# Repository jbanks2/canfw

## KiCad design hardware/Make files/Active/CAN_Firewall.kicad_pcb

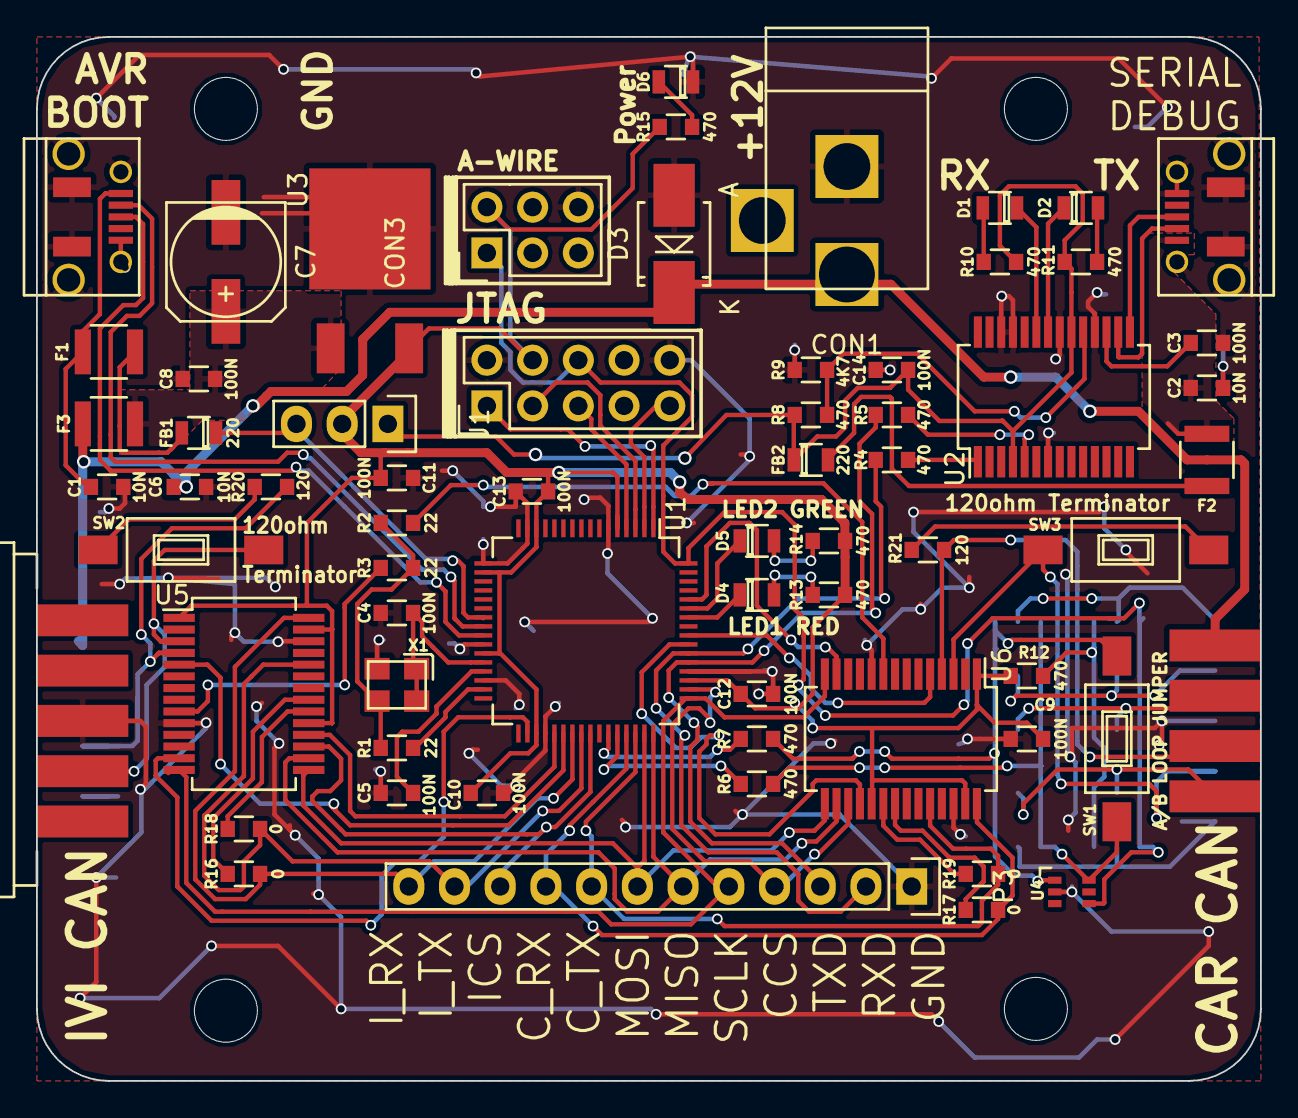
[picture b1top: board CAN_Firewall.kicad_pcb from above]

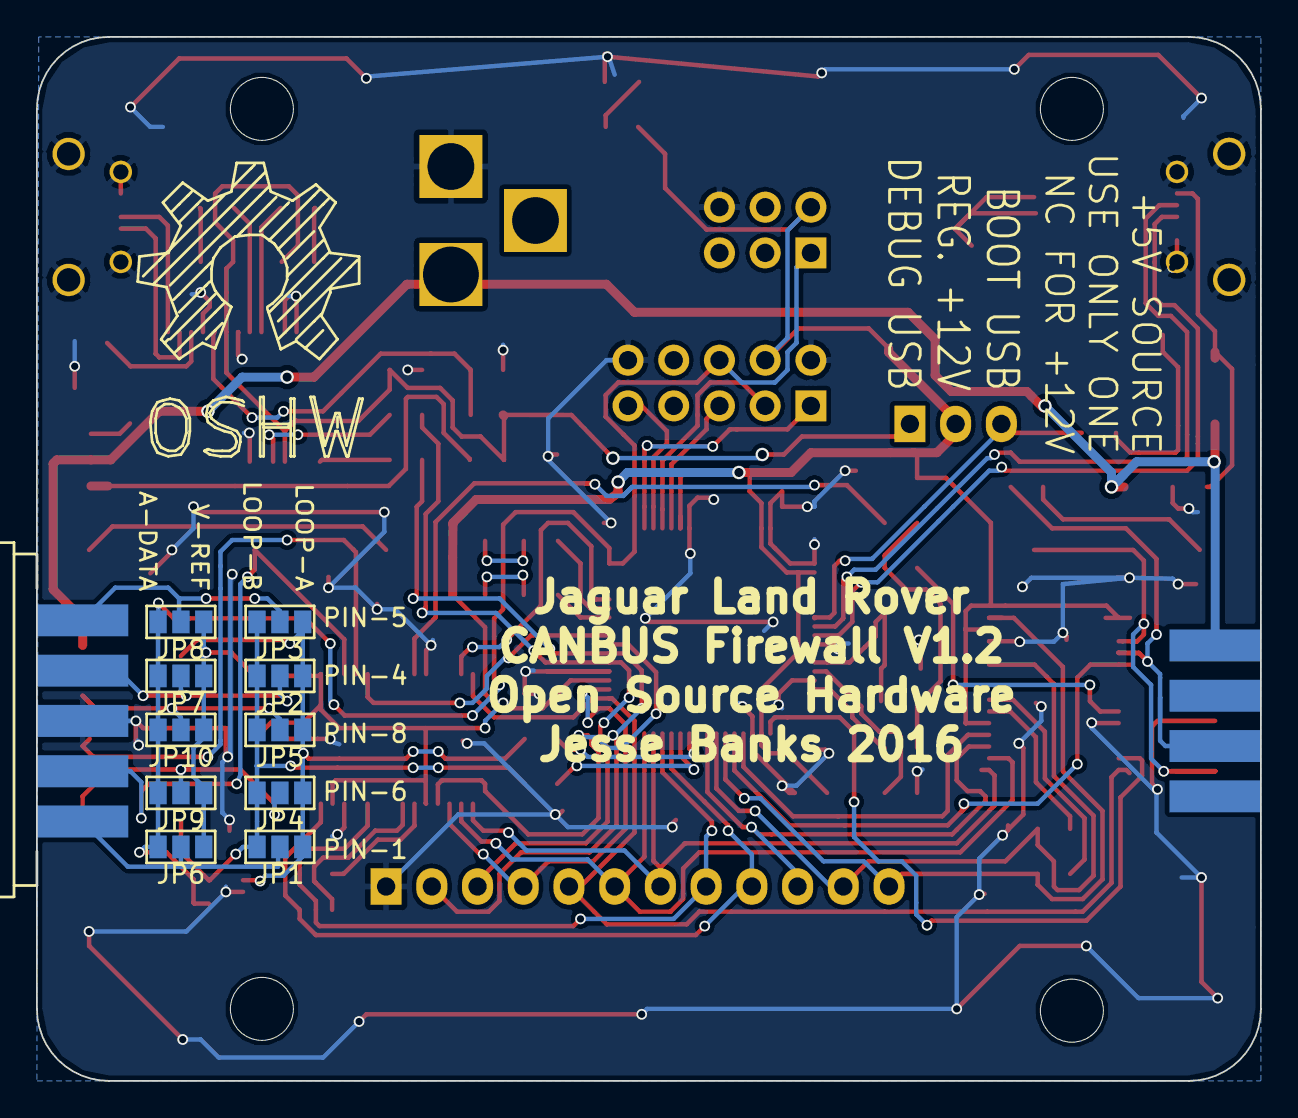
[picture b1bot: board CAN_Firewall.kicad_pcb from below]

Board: 2 copper layers, 68.0 x 58.0 mm, 75 parts (11 on the bottom side), 75 nets.

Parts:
C1, C2, C6: 10N; R_0603_sm
C3, C4, C5, C8, C9, C10, C11, C12, C13, C14: 100N; R_0603_sm
C7: 47U; c_elec_6.3x5.3
CON1: BARREL_JACK
CON2: AVR-JTAG-10; Pin_Header_Straight_2x05
CON3: AVR-AW-6; Pin_Header_Straight_2x03
D1: YELLOW; Diode_0805_12
D2: WHITE; Diode_0805_12
D3: SMBJ16A; SMB_Handsoldering
D4: RED; Diode_0805_12
D5: GREEN; Diode_0805_12
D6: BLUE; Diode_0805_12
F1, F2, F3: FUSE; R_1210_SM
FB1, FB2: 220; Diode_0805_12_SM
J1: +5V_SRC; Pin_Header_Straight_1x03
J2, J3: DB9; DB9F_CI
JP1, JP6: Matrix A; GS3
JP2, JP7: Matrix B; GS3
JP3, JP8: Matrix C; GS3
JP4, JP9: Matrix D; GS3
JP5, JP10: Matrix E; GS3
P1, P2: USB_OTG; USB_Micro-B-DX4R005JJ2R1800
P3: DIAG Port; Pin_Header_Straight_1x12
R1, R2, R3: 22; R_0603_sm
R4, R5, R6, R7, R8, R10, R11, R12, R13, R14, R15: 470; R_0603_sm
R9: 4K7; R_0603_sm
R16, R17, R18, R19: 0; R_0603_sm
R20, R21: 120; R_0603_sm
SW1, SW2, SW3: SPST; SW_SPST_FSMSM_SM
U1: AT32UC3C; LQFP-64_10x10mm_Pitch0.5mm
U2: FT232RL-SSOP; SSOP-28_5.3x10.2mm_Pitch0.65mm
U3: MC78M05CDT; D-Pak_TO252AA
U4: SMF05; SC-70-6
U5, U6: MCP25625; SSOP-28_5.3x10.2mm_Pitch0.65mm
X1: TXC

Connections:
+3V3: C4.1, U1.28, X1.1, X1.4
+5V: C9.1, C10.1, C11.1, C12.1, C13.1, CON2.4, CON3.2, J1.2, R12.2, R13.2, R14.2, R15.2, U1.5, U1.14, U1.18, U1.27, U1.35, U1.51, U3.3, U5.1, U5.19, U5.27, U6.1, U6.19, U6.27
+12V: C6.1, CON1.1, D3.1, F3.1, J2.9, J3.9
A: J3.1, JP1.2, JP6.2
B: J3.4, JP2.2, JP7.2
C: J3.5, JP3.2, JP8.2
CAR_CANH: J3.7, R21.2, U6.4
CAR_CANL: J3.2, SW3.2, U6.3
CAR_CS: P3.4, U1.50, U6.17
CAR_INT: U1.60, U6.13
CAR_RESET: U1.55, U6.18
CAR_RxCAN: P3.9, R17.1, U1.45, U6.28
CAR_STBY: U1.56, U6.5
CAR_TxCAN: P3.8, R19.1, U1.46, U6.24
CLK1: R1.1, U1.31
CLK2: R2.1, U6.9
CLK3: R3.1, U5.9
D: J3.6, JP4.2, JP9.2
E: J3.8, JP5.2, JP10.2
GND: C1.2, C2.2, C3.2, C4.2, C5.2, C6.2, C7.2, C8.2, C9.2, C10.2, C11.2, C12.2, C13.2, C14.2, CON1.2, CON2.2, CON2.10, CON3.6, D3.2, D6.1, J2.3, J3.3, P1.5, P1.6, P2.5, P2.6, P3.1, R9.2, U1.6, U1.15, U1.17, U1.26, U1.30, U1.36, U1.52, U2.7, U2.18, U2.21, U2.25, U2.26, U3.4, U4.2, U5.10, U5.26, U6.10, U6.26, X1.2
IVI_CANH: J2.7, R20.2, U5.4
IVI_CANL: J2.2, SW2.2, U5.3
IVI_CS: P3.10, U1.41, U5.17
IVI_INT: U1.34, U5.13
IVI_RESET: U1.37, U5.18
IVI_RxCAN: P3.12, R16.1, U1.39, U5.28
IVI_STBY: U1.38, U5.5
IVI_TxCAN: P3.11, R18.1, U1.40, U5.24
LED1: D4.1, U1.58
LED2: D5.1, U1.59
LOOP_A: JP1.1, JP2.1, JP3.1, JP4.1, JP5.1, R7.1, SW1.2, U4.1
LOOP_B: JP1.3, JP2.3, JP3.3, JP4.3, JP5.3, R6.1, SW1.1, U4.6
MISO: P3.6, U1.48, U5.16, U6.16
MOSI: P3.7, U1.47, U5.15, U6.15
unnamed: C1.1, F1.2, P1.1
unnamed: C2.1, F2.2, P2.1
unnamed: C3.1, U2.17
unnamed: C5.1, U1.29
unnamed: C7.1, C8.1, F3.2, U3.1
unnamed: D1.1, U2.23
unnamed: D1.2, R10.1
unnamed: D2.1, U2.22
unnamed: D2.2, R11.1
unnamed: D4.2, R13.1
unnamed: D5.2, R14.1
unnamed: D6.2, R15.1
unnamed: F1.1, FB1.2
unnamed: F2.1, FB2.2
unnamed: JP6.1, JP7.1, JP8.1, JP9.1, JP10.1, R12.1
unnamed: R1.2, R2.2, R3.2, X1.3
unnamed: R4.2, U2.1
unnamed: R5.2, U2.5
unnamed: R6.2, U1.44
unnamed: R7.2, U1.43
unnamed: R8.1, R9.1, U2.19
unnamed: R16.2, U5.21
unnamed: R17.2, U6.21
unnamed: R18.2, U5.20
unnamed: R19.2, U6.20
unnamed: R20.1, SW2.1
unnamed: R21.1, SW3.1
RX_DBG: P3.2, R4.1, U1.54
SCLK: P3.5, U1.49, U5.14, U6.14
TCK: CON2.1, U1.1
TDI: CON2.9, U1.2
TDO: CON2.3, U1.3
TMS: CON2.5, U1.4
TX_DBG: P3.3, R5.1, U1.53
USB5: C14.1, FB2.1, J1.1, R8.2, R10.2, R11.2, U2.4, U2.20
USB+: P2.3, U2.15
USB-: P2.2, U2.16
USBM: P1.2, U1.24
USBP: P1.3, U1.25
VBUS: FB1.1, J1.3, U1.23
~RESET/A_DATA: CON2.6, CON3.1, JP6.3, JP7.3, JP8.3, JP9.3, JP10.3, U1.64, U4.4

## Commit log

2015-12-18 V1.2 PCB Redsign
2015-12-18 Optimization of: route, silk, 3d
2015-12-22 Minor chages
2015-12-22 minor improvements
